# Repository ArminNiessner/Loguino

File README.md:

# Loguino

The Loguino is a low budget and open-source data acquisition device based on an Arduino Pro Mini and designed for monitoring e.g. tree growth dynamics, climate or other environmental parameters at remote locations. It is capable of reading analog inputs as voltage signals at a resolution of 18-bit and almost any kind of digital sensors can be connected using standard protocols (e.g. I²C, SPI, 1-Wire or SDI-12). Logging interval can be set from some seconds to hours and data are stored as comma seperated .csv file to a 4GB (or 8GB) micro sd-card. Therefore, no special software or hardware is needed to readout the Loguino. While the Loguino is in a low power sleep mode in between logs, consuming only about 100µA, a Real-Time-Clock Module (RTC DS3231) keeps track of time and wakens the Loguino for the next log event. Interrupts can independently be counted without interrupting main routines, in order to monitor rainfall or windspeed. The Loguino board togheter with a standard Lithium-Ion 18650 battery (keeps the Loguino running for about a year) is mounted within a rugged enclosure (IP65) that can be attached to a tree or pole, for instance.

The eagle files for the PCB are available in this repository and all parts are easily available on the internet, however, ready-to-use (assembled, programmed and tested) Loguinos are for sale by sending a request to armin.niessner@taysira.org. All Arduino libraries and sketches needed for operation of the Loguino are available in this repository or at other git repositories (listed below). The Arduino software needed to program the Loguino is available at [Arduino](https://www.arduino.cc/).

# Parts

* Arduino Pro Mini 3.3V, 8MHz, ATmega328 (e.g. [Amazon](https://www.amazon.de/gp/product/B078H9RMZY/ref=ppx_yo_dt_b_asin_title_o07_s01?ie=UTF8&psc=1))

* FTDI Adapter FT232RL USB to TTL Serial (3.3V, 5V) (e.g. [Amazon](https://www.amazon.de/AZDelivery-Adapter-FT232RL-Serial-gratis/dp/B01N9RZK6I/ref=sr_1_3?__mk_de_DE=%C3%85M%C3%85%C5%BD%C3%95%C3%91&keywords=FTDI&qid=1555957551&s=computers&sr=1-3))

* SPI micro sd-card shield (e.g. [Amazon](https://www.amazon.de/gp/product/B077MB17JB/ref=ppx_yo_dt_b_asin_title_o07_s00?ie=UTF8&psc=1))

* Real-Time-Clock RTC DS3231 (e.g. [Amazon](https://www.amazon.de/gp/product/B076GP5B94/ref=ppx_yo_dt_b_asin_title_o07_s02?ie=UTF8&psc=1))

* ADC MCP3424 (SOIC 14) 

* Screw terminals (5 x 5.08 mm 2pins, 4 x 2.54 mm 4 pins, 1 x 2.54 mm 3 pins, 1 x 2.54 mm 2 pins)

* Socket strip (6 pins, to connect the FTDI adapter)

* Pin strip (51 pins in total to place the Arduino Pro Mini onto the PCB and for placing the jumpers)

* Jumper (maximum 5)

* Resistors (2 x 10 KOhm, 3 x 4.7 KOhm, 4 x 2.2 KOhm)

* Ceramic capacitors (1 x 100 nF, 4 x 3.3 nF)

* Electrolytic capacitor (1 x 10µF)

* Micro sd-card (4 GB or 8 GB, quality may differ significantly between different manufacturer and even production lines, leading to a higher power consumption during sleep mode. I use and recommend Transcend TS4GUSDC4 Micro SDHC 4GB Class 4)

* Li-ion 18650 battery

* Li-ion 18650 battery tray

* Enclosure (Bopla ET 215 120 x 80 x 57)

* Cable glands (1-x, depending on number of cables to enter the enclosure)

* PCB (eagle files available in this repository or contact armin.niessner@taysira.org)

# Assembly

1. Solder the Arduino Mini Pro Board on to the PCB using pins.

1. Remove the power LED and voltage regulator on the Arduino Pro Mini.

1. Solder the socket strip next to the Arduino Pro Mini for connection to the FTDI. Test the Arduino by uploading the first test sketch ("test_1_arduino.ino") and check the serial monitor for the output.

1. Prepare soldering areas for the ADC on the PCB with soldering fluid and solder the ADC MCP3424 onto the PCB.

1. Solder the two 4.7K Resistors, the 0.1µF ceramic capacitor, the 10µF ELKO and two pins next to the ADC. Place a bridge on the two pins.

1. Upload test script "test_2_adc.ino" and open serial monitor. The serial monitor should show random numbers for all four channels.

1. Solder all screw terminals, resistors, capacitors and pins onto PCB.

1. Repeat ADC test.

1. Remove voltage regulator from the SD-card-module, connect lower two pins with a piece of wire and remove the overlapping part of the SD-module-PCB under the pins using a "Dremel".

1. Solder the SD-module to the PCB and test it by uploading the test script "test_3_sd.ino". Check the serial monitor for error messages.

1. Remove the LED and upper resistor-IC from the RTC-module and solder the RTC-module to the PCB. Test it by uploading the script "test_4_rtc.ino" and check the serial monitor.

# Sensors

### Dendrometer (linear displacement potentiometer, MMR10_11 R5K, Megatron Elektronik AG & Co, Munich, Germany):

* Green = `ADC0 +` (left)

* Yellow = `ADC0 -` (middle)

* Red = `ADC1 +` (right)

* Connect `ADC0 -` and `ADC1 -` to GND (place jumper as shown in the picture above) 

Example sketch: [Loguino_dd_dd](https://github.com/ArminNiessner/Loguino/tree/master/sketches/Examples/Loguino_dd_dd/Loguino_dd_dd.ino)

### Thermocouple (Granier-sap-flow sensor):

* Connect one end to e.g. `ADC0 +` and the other end to `ADC0 -`

* leave the jumper at `ADC0 -` open

Example sketch: [Loguino_4xyl](https://github.com/ArminNiessner/Loguino/tree/master/sketches/Examples/Loguino_4xyl/Loguino_4xyl.ino)

### DS18S20 temperature:

* GND = `-` (right)

* VCC = `+` (middle)

* DATA = `D` (left)

Example sketch: [Loguino_dd_xyl_t](https://github.com/ArminNiessner/Loguino/tree/master/sketches/Examples/Loguino_dd_xyl_t/Loguino_dd_xyl_t.ino)

### DHT22 T/RH sensor:

* GND = `-` (right)
* VCC = `+` (second from right)
* Data = `D` (second from left)

Example sketch: [Loguino_DHT](https://github.com/ArminNiessner/Loguino/tree/master/sketches/Examples/Loguino_DHT/Loguino_DHT.ino)

### SHT7x Sensirion T/RH sensor:

* SCK = `C` (left, to Pin 7

* DATA = `D` (second from left)

* VCC = `+` (second from right)

* GND = `-` (right)

Example sketch: [Loguino_SHT](https://github.com/ArminNiessner/Loguino/tree/master/sketches/Examples/Loguino_SHT/Loguino_SHT.ino)

### BME280 T/RH/Pressure sensor:

* VCC = `+` (top)
* GND = `-` (second from top)
* SCL = `SCL` (third from top)
* SDA = `SDA` (third from bottom)

Example sketch: [Loguino_BME](https://github.com/ArminNiessner/Loguino/tree/master/sketches/Examples/Loguino_BME/Loguino_BME.ino)

# Software set up and programming the Loguino

1. Download and install the latest version of the [Arduino software](https://www.arduino.cc/en/Main/Software)
1. Download this repository (click on the green "clone"-button at the top of this web page) and copy all the folders in "libraries" from this repository to the "libraries"-folder in your Arduino installation folder.
1. Get the libraries [AVRUtils](https://github.com/SConaway/AVRUtils), [LowPower](https://github.com/rocketscream/Low-Power) and [SdFat](https://github.com/greiman/SdFat)
and copy them to the "libraries"-folder. If you want to use a DS18S20 temperature sensor or other digital sensors you have to get the corresponding library, listed below in the Libraries section.
1. Open one of the example scripts in the folder "sketches" from the Logiuno repository using the Arduino software. Go to "Tools" and 
set "Board" to "Arduino Pro or Pro Mini". Go again to "Tools" and set "Processor" to "ATmega 328P (3.3V, 8MHz)".
1. Connect the FTDI Adapter to the Loguino board, upper side facing the Arduino Pro Mini. Make sure
that the jumper on the FTDI Adapter is set to 3.3V and the battery is not connected to the Loguino. Connect the usb to a usb port and go to "Tools"
and set "Port" to the appropiate port (e.g. COM3). If you are using windows, you probably first need to download and install a driver for the FTDI Adapter
(e.g. [here](https://www.campbellsci.com/downloads/usb-to-serial-driver-ftdi-chip-set)).
1. "Upload" the sketch (right arrow button) and wait until the sketch is compiled and uploaded.
Open the "Serial Monitor" (button at the upper right corner) and check the output.

## Setting the time
1. Use the [test_4_rtc.ino](https://github.com/ArminNiessner/Loguino/tree/master/sketches/Tests/test_4_rtc/test_4_rtc.ino)
to set the RTC to your system time.
2. Upload the sketch, comment `RTC.adjust(DateTime(__DATE__, __TIME__));` and upload the sketch again. The second 
upload with `//RTC.adjust(DateTime(__DATE__, __TIME__));` should be right after the first upload was finished, in order
to have only a short delay between RTC time and system time (usually less than 10 seconds).

## Final setup
Choose an appropiate example sketch from this repository and adjust it to your sensor setup:

* `uint8_t Log_Interval_Minutes = 1;` set to the desired logging intervall in minutes
* `String file_ini = "Lg0001";` set to the appropiate Logger ID
* If you want that logging starts at the next full minute, next full 10 minute (:00, :10, :20, ..),
next full half hour (:00, :30) or the next full hour, you can uncomment the appropiate block of coder
under `void setup() {....}` and uncomment the other blocks. 

Upload the sketch and your Loguino is ready to go.

## Libraries

* AVRUtils ([Git](https://github.com/SConaway/AVRUtils)) - measure supply voltage

* SPI ([Arduino](https://www.arduino.cc/en/reference/SPI)) - communication with SD-card module

* SdFat ([Git](https://github.com/greiman/SdFat)) - read and write to SD-card

* Wire ([Arduino](https://www.arduino.cc/en/reference/wire)) - communication with I²C devices e.g. the MCP3424

* LowPower ([Git](https://github.com/rocketscream/Low-Power)) - low power library to set Loguino to sleep

* ANiess (available in this repository) - main library for Loguino

* AN_RTClib (available in this repository) - library to interact with RTC

* MCP342x (available in this repository) - library to interact with the ADC

* DallasTemperature ([Git](https://github.com/milesburton/Arduino-Temperature-Control-Library))- library to interact with the DS18S20 temperature sensor

* Sensirion ([Git](https://github.com/spease/Sensirion)) - library to interact with the SHT75 T/RH sensor

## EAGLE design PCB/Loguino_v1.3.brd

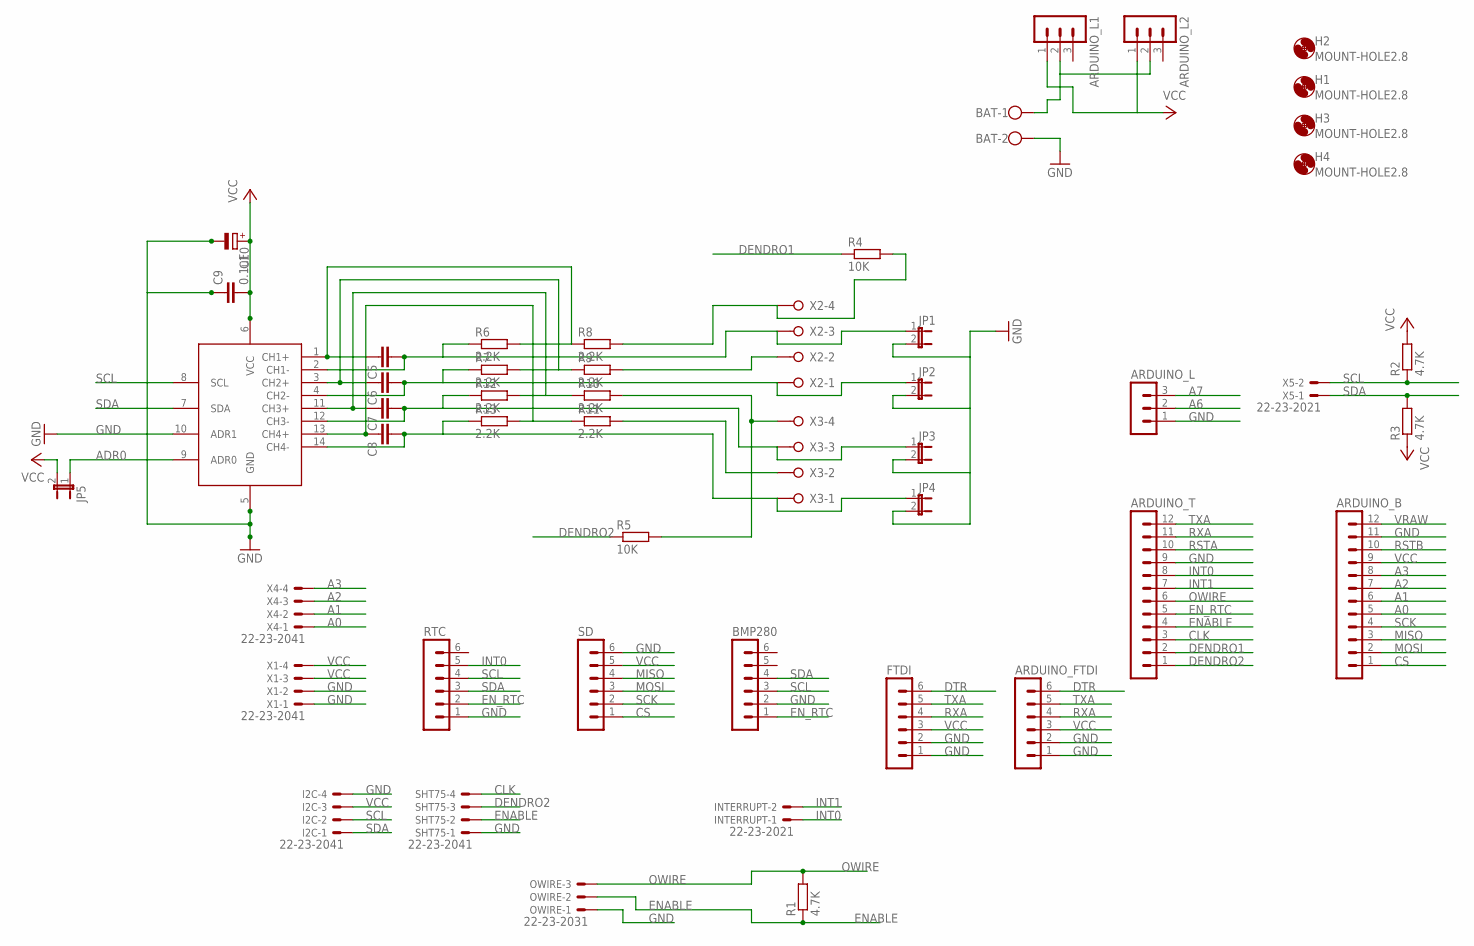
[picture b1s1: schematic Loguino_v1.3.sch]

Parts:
ARDUINO_B: MA12-1
ARDUINO_FTDI: MA06-1
ARDUINO_L, ARDUINO_L1, ARDUINO_L2: MA03-1
ARDUINO_T: MA12-1
BAT: W237-102
BMP280: MA06-1
C5, C6, C7, C8: C-EU025-024X044; C025-024X044
C9: 0.1uF; C050-025X075
C10: CPOL-EUE2,5-6E; E2,5-6E
FTDI: MA06-1
H1, H2, H3, H4: MOUNT-HOLE2.8; 2,8
I2C: 22-23-2041
INTERRUPT: 22-23-2021
JP1, JP2, JP3, JP4, JP5: JP1E; JP1
OWIRE: 22-23-2031
R1, R2, R3: 4.7K; 0204/7
R4, R5: 10K; 0207/10
R6, R7, R8, R9, R10, R11, R12, R13: 2.2K; 0207/10
RTC: MA06-1
SD: MA06-1
SHT75: 22-23-2041
U$2: MCP342; SO14
X1, X4: 22-23-2041
X2, X3: W237-04P; W237-4P
X5: 22-23-2021

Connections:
A0: ARDUINO_B.5, X4.1
A1: ARDUINO_B.6, X4.2
A2: ARDUINO_B.7, X4.3
A3: ARDUINO_B.8, X4.4
A6: ARDUINO_L.2
A7: ARDUINO_L.3
ADR0: JP5.1, U$2.9 (ADR0)
CLK: ARDUINO_T.3, SHT75.4
CS: ARDUINO_B.1, SD.1
DENDRO1: ARDUINO_T.2, R4.1
DENDRO2: ARDUINO_T.1, R5.1, SHT75.3
DTR: ARDUINO_FTDI.6, FTDI.6
ENABLE: ARDUINO_T.4, OWIRE.2, R1.1, SHT75.2
EN_RTC: ARDUINO_T.5, BMP280.1, RTC.2
GND: ARDUINO_B.11, ARDUINO_FTDI.1, ARDUINO_FTDI.2, ARDUINO_L.1, ARDUINO_T.9, BAT.2, BMP280.2, C9.1, C10.-, FTDI.1, FTDI.2, I2C.4, JP1.2, JP2.2, JP3.2, JP4.2, OWIRE.1, RTC.1, SD.6, SHT75.1, U$2.5 (GND), U$2.10 (ADR1), X1.1, X1.2
INT0: ARDUINO_T.8, INTERRUPT.1, RTC.5
INT1: ARDUINO_T.7, INTERRUPT.2
MISO: ARDUINO_B.3, SD.4
MOSI: ARDUINO_B.2, SD.3
unnamed: ARDUINO_L1.2, ARDUINO_L2.2, BAT.1
unnamed: C5.2, JP1.1, R6.1, U$2.2 (CH1-), X2.3
unnamed: R4.2, R8.2, X2.4
unnamed: R9.2, X2.2
unnamed: R5.2, R10.2, X3.4
unnamed: R11.2, X3.2
unnamed: C5.1, R6.2, R8.1, U$2.1 (CH1+)
unnamed: C6.1, R7.2, R9.1, U$2.3 (CH2+)
unnamed: C7.1, R10.1, R12.2, U$2.11 (CH3+)
unnamed: C8.1, R11.1, R13.2, U$2.13 (CH4+)
unnamed: C6.2, JP2.1, R7.1, U$2.4 (CH2-), X2.1
unnamed: C7.2, JP3.1, R12.1, U$2.12 (CH3-), X3.3
unnamed: C8.2, JP4.1, R13.1, U$2.14 (CH4-), X3.1
OWIRE: ARDUINO_T.6, OWIRE.3, R1.2
RSTA: ARDUINO_T.10
RSTB: ARDUINO_B.10
RXA: ARDUINO_FTDI.4, ARDUINO_T.11, FTDI.4
SCK: ARDUINO_B.4, SD.2
SCL: BMP280.3, I2C.2, R2.1, RTC.4, U$2.8 (SCL), X5.2
SDA: BMP280.4, I2C.1, R3.2, RTC.3, U$2.7 (SDA), X5.1
TXA: ARDUINO_FTDI.5, ARDUINO_T.12, FTDI.5
VCC: ARDUINO_B.9, ARDUINO_FTDI.3, ARDUINO_L1.1, ARDUINO_L2.1, C9.2, C10.+, FTDI.3, I2C.3, JP5.2, R2.2, R3.1, SD.5, U$2.6 (VCC), X1.3, X1.4
VRAW: ARDUINO_B.12

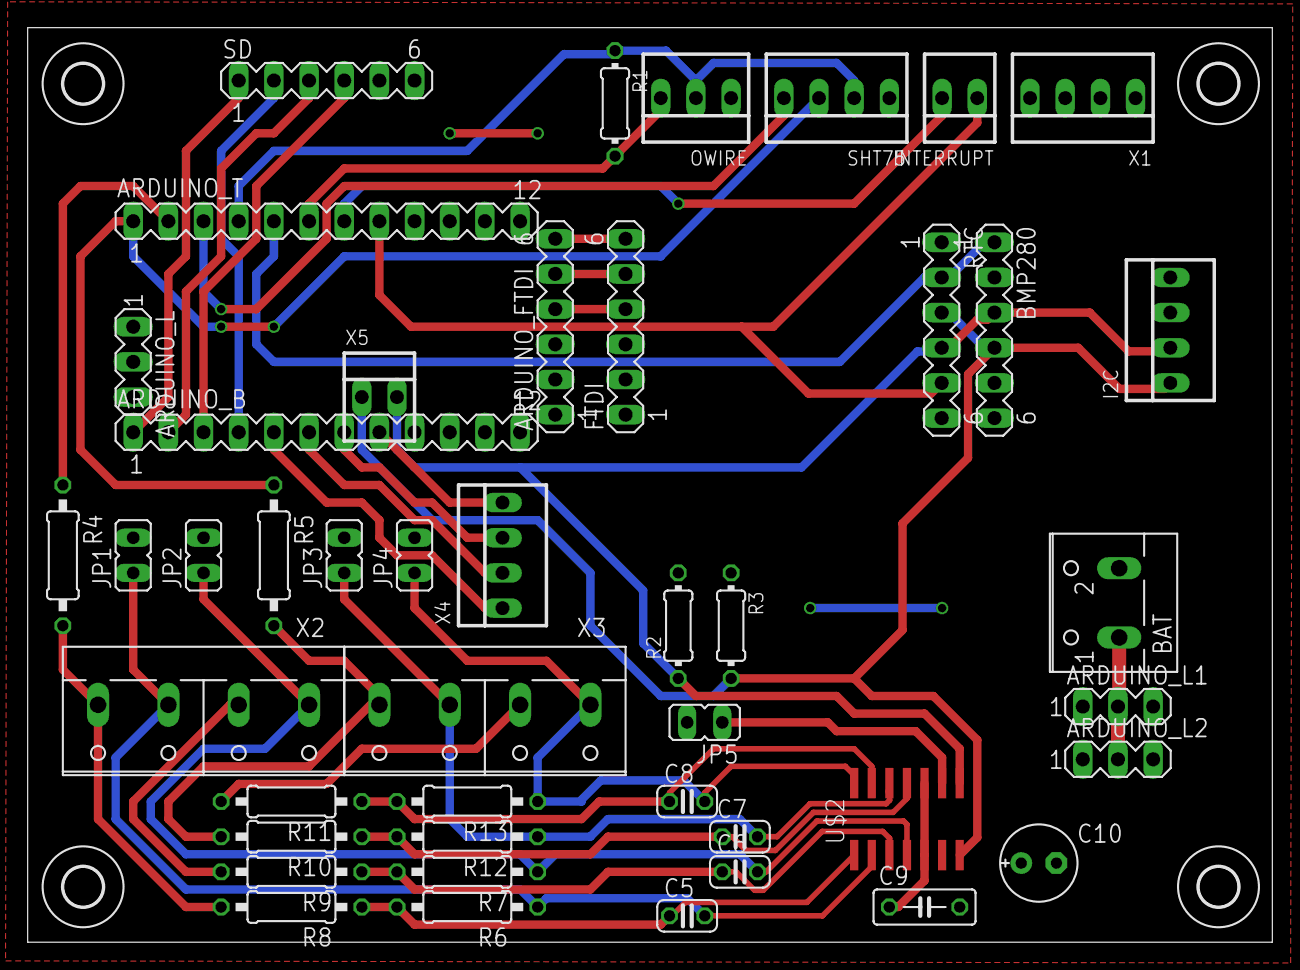
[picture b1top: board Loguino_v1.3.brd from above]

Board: 2 copper layers, 89.9 x 66.0 mm, 49 parts (0 on the bottom side), 37 nets.

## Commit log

2019-04-22 README edit
2019-04-22 Libraries foArduino added
2019-04-22 sketches for Arduino added
2019-04-22 eagle PCB files added
2019-04-22 added GNU Licence texts to sketches
2019-04-22 README edit Loguino
2019-04-24 removal of unneeded lines
2019-04-24 picture with a Loguino installed at a tree
2019-04-24 deleted pic
2019-04-27 schematic png and .gitignore added
2019-04-27 DOI added
2019-05-12 SHT75 added
2019-10-19 Logo
2019-12-03 default sketch
2020-03-26 updated PCB and sketches to v1.3
2020-04-04 sketches and readme updated
2020-06-19 README extended
2020-06-29 README updated
